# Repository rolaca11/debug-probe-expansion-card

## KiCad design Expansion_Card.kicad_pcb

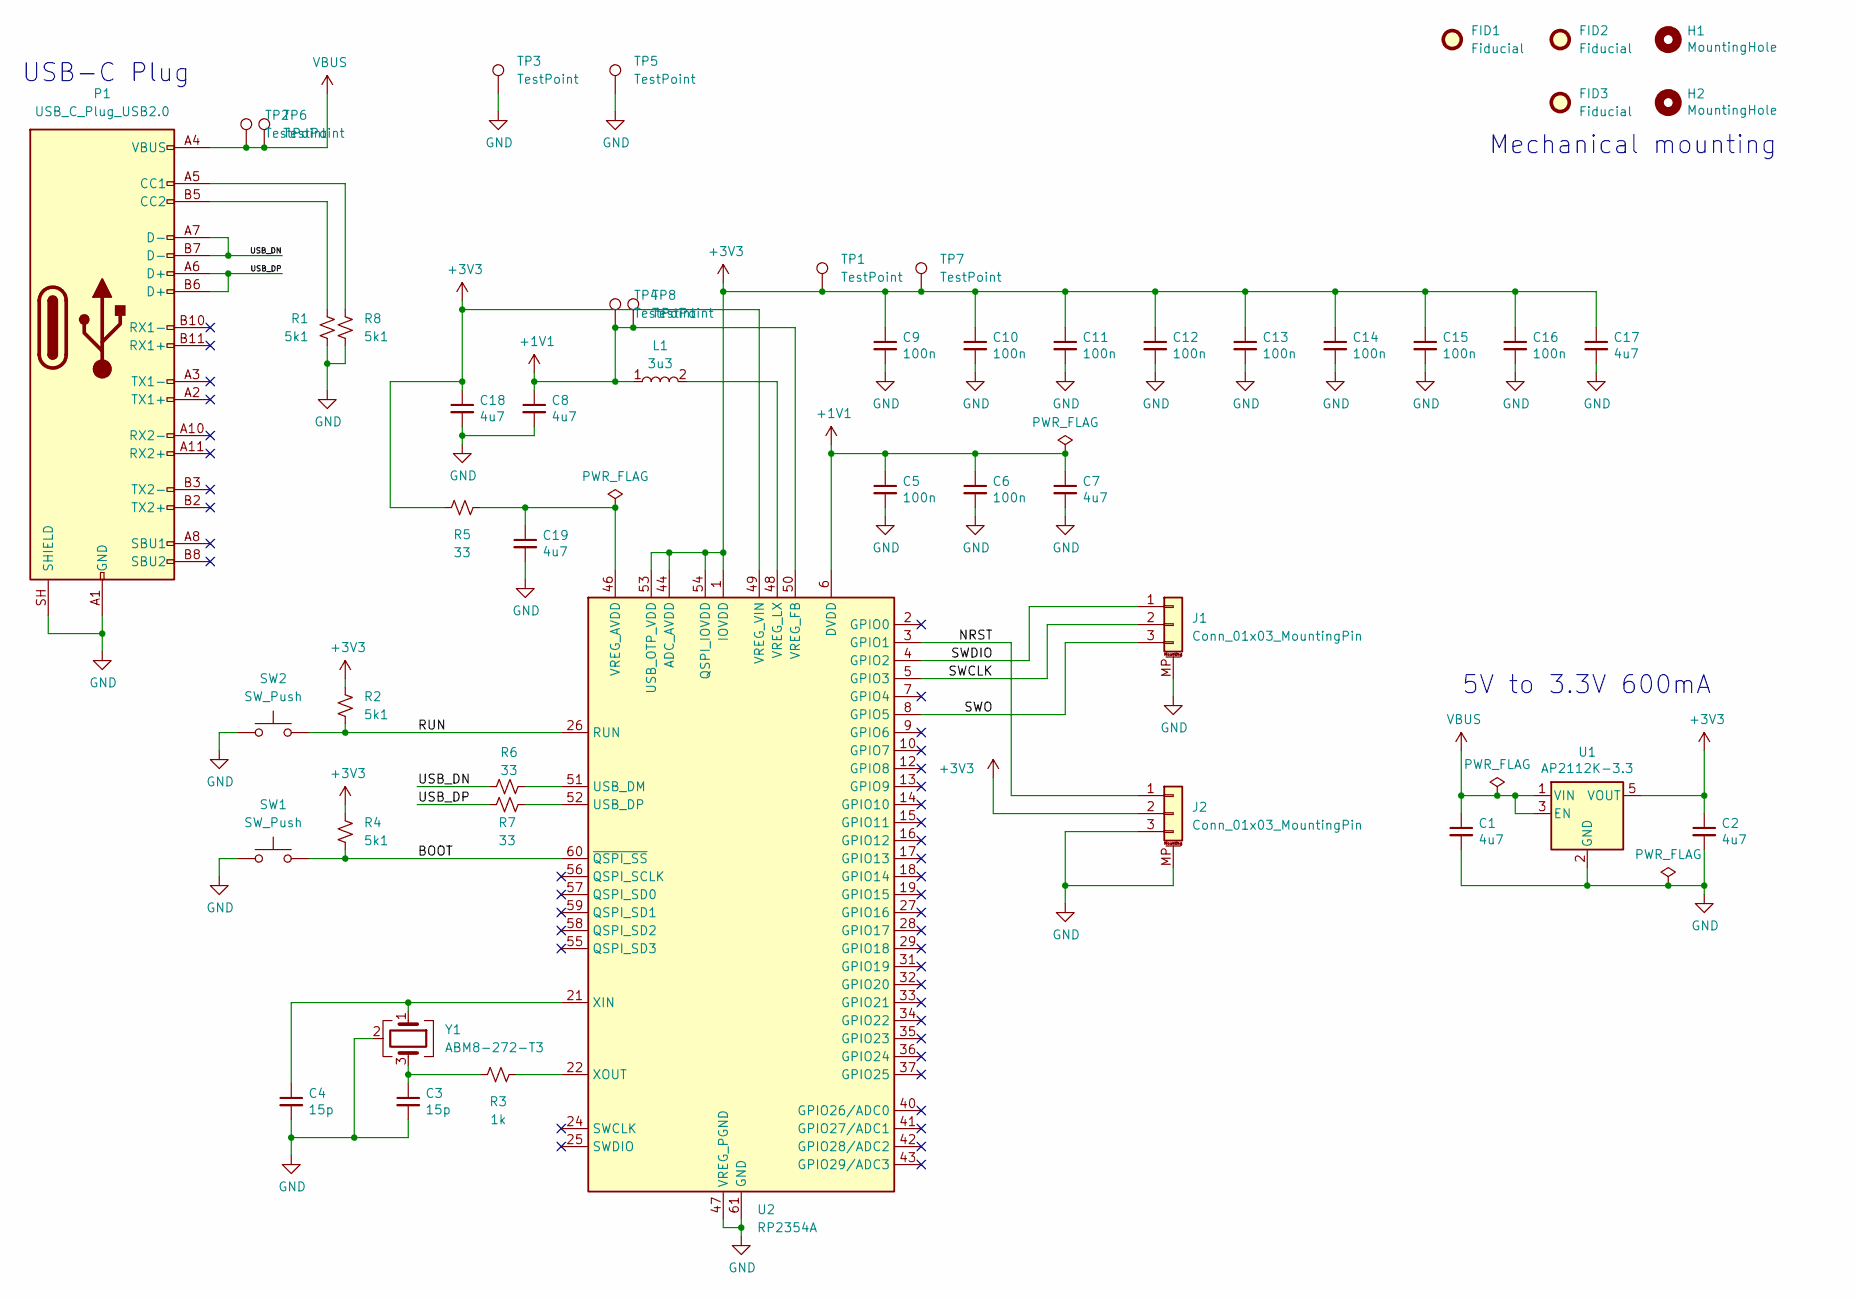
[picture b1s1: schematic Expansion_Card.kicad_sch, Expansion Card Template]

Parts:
C1, C2, C7, C8, C17, C18, C19: 4u7; C_0402_1005Metric; MPN CL05A475MP5NRNC; JLCPCB Part # C23733
C3, C4: 15p; C_0402_1005Metric; MPN 0402CG150J500NT; JLCPCB Part # C1548
C5, C6, C9, C10, C11, C12, C13, C14, C15, C16: 100n; C_0402_1005Metric; MPN CL05B104KO5NNNC; JLCPCB Part # C1525
FID1, FID2, FID3: Fiducial; Fiducial_1mm_Mask2mm
H1, H2: MountingHole; MountingHole_2.2mm_M2
J1, J2: Conn_01x03_MountingPin; JST_SH_SM03B-SRSS-TB_1x03-1MP_P1.00mm_Horizontal; MPN SM03B-SRSS-TB(LF)(SN); JLCPCB Part # C160403
L1: 3u3; AOTAB201610S3R3101T; MPN AOTA-B201610S3R3-101-T; JLCPCB Part # C42411119
P1: USB_C_Plug_USB2.0; USB_C_Plug_Molex_105444; MPN 1054440001; JLCPCB Part # C134082
R1, R2, R4, R8: 5k1; R_0402_1005Metric; MPN 0402WGF5101TCE; JLCPCB Part # C25905
R3: 1k; R_0402_1005Metric; MPN 0402WGF1001TCE; JLCPCB Part # C11702
R5, R6, R7: 33; R_0402_1005Metric; MPN 0402WGF330JTCE; JLCPCB Part # C25105
SW1, SW2: SW_Push; SW_SPST_B3U-1000P-B; MPN B3U-1000P; JLCPCB Part # C231329
TP1, TP2, TP3, TP4, TP5, TP6, TP7, TP8: TestPoint; TestPoint_Pad_D1.5mm
U1: AP2112K-3.3; SOT-23-5; MPN AP2112K-3.3TRG1; JLCPCB Part # C23380830
U2: RP2354A; QFN-60-1EP_7x7mm_P0.4mm_EP3.4x3.4mm; MPN RP2354A; JLCPCB Part # C41378174
Y1: ABM8-272-T3; Crystal_SMD_3225-4Pin_3.2x2.5mm; MPN ABM8-272-T3; JLCPCB Part # C20625731

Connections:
+1V1: C5.1, C6.1, C7.1, C8.1, L1.1, TP4.1 (1_1), TP8.1 (1_1), U2.6 (DVDD), U2.23 (DVDD), U2.39 (DVDD), U2.50 (VREG_FB)
+3V3: C2.1, C9.1, C10.1, C11.1, C12.1, C13.1, C14.1, C15.1, C16.1, C17.1, C18.1, J2.2, R2.2, R4.2, R5.1, TP1.1 (1_1), TP7.1 (1_1), U1.5 (VOUT), U2.1 (IOVDD), U2.11 (IOVDD), U2.20 (IOVDD), U2.30 (IOVDD), U2.38 (IOVDD), U2.44 (ADC_AVDD), U2.45 (IOVDD), U2.49 (VREG_VIN), U2.53 (USB_OTP_VDD), U2.54 (QSPI_IOVDD)
/BOOT: R4.1, SW1.2, U2.60 (~QSPI_SS)
/NRST: J2.1, U2.3 (GPIO1)
/RUN: R2.1, SW2.1, U2.26 (RUN)
/SWCLK: J1.2, U2.5 (GPIO3)
/SWDIO: J1.1, U2.4 (GPIO2)
/SWO: J1.3, U2.8 (GPIO5)
/USB_DN: P1.A7 (D-), P1.B7 (D-), R6.2
/USB_DP: P1.A6 (D+), P1.B6 (D+), R7.2
GND: C1.2, C2.2, C3.2, C4.2, C5.2, C6.2, C7.2, C8.2, C9.2, C10.2, C11.2, C12.2, C13.2, C14.2, C15.2, C16.2, C17.2, C18.2, C19.2, J1.MP (MountPin), J2.3, J2.MP (MountPin), P1.A1 (GND), P1.A12 (GND), P1.B1 (GND), P1.B12 (GND), P1.SH (SHIELD), R1.1, R8.2, SW1.1, SW2.2, TP3.1 (1_1), TP5.1 (1_1), U1.2 (GND), U2.47 (VREG_PGND), U2.61 (GND), Y1.2 (G), Y1.4 (G)
unnamed: C3.1, R3.1, Y1.3
unnamed: P1.A5 (CC1), R8.1
unnamed: P1.B5 (CC2), R1.2
unnamed: R6.1, U2.51 (USB_DM)
unnamed: R7.1, U2.52 (USB_DP)
unnamed: C19.1, R5.2, U2.46 (VREG_AVDD)
unnamed: L1.2, U2.48 (VREG_LX)
unnamed: C4.1, U2.21 (XIN), Y1.1
unnamed: R3.2, U2.22 (XOUT)
VBUS: C1.1, P1.A4 (VBUS), P1.A9 (VBUS), P1.B4 (VBUS), P1.B9 (VBUS), TP2.1 (1_1), TP6.1 (1_1), U1.1 (VIN), U1.3 (EN)

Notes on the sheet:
Mechanical mounting
USB-C Plug
5V to 3.3V 600mA

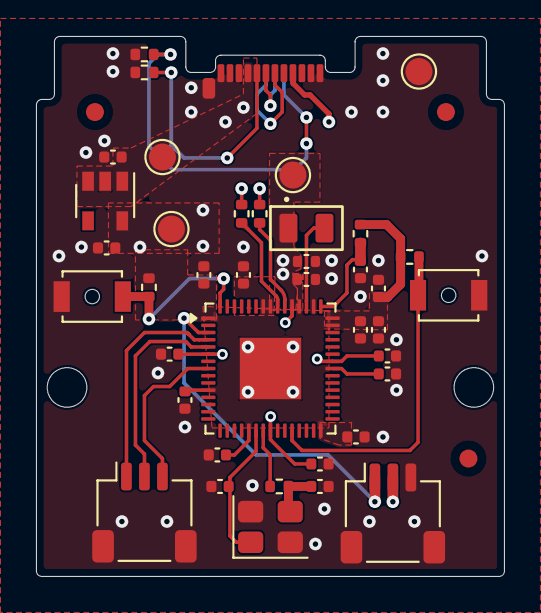
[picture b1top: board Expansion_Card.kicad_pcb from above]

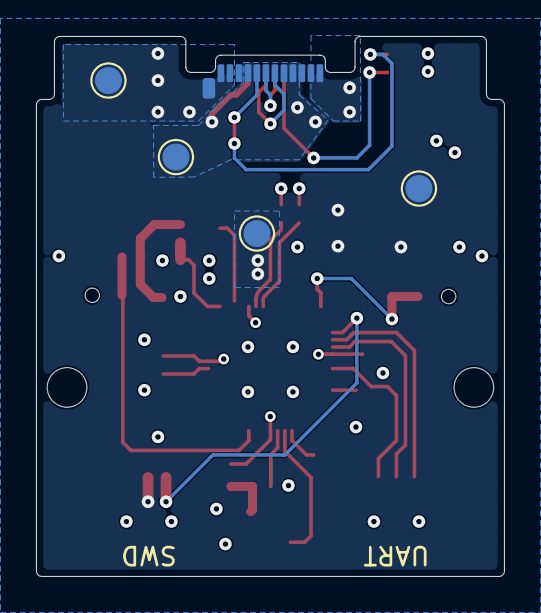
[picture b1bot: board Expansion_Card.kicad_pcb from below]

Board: 4 copper layers, 26.0 x 30.0 mm, 49 parts (4 on the bottom side), 21 nets.

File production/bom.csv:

Designator,Footprint,Quantity,Value,LCSC Part #
"C1, C17, C18, C19, C2, C7, C8",0402,7,4u7,C23733
"C10, C11, C12, C13, C14, C15, C16, C5, C6, C9",0402,10,100n,C1525
"C3, C4",0402,2,15p,C1548
"J1, J2",JST_SH_SM03B-SRSS-TB_1x03-1MP_P1.00mm_Horizontal,2,Conn_01x03_MountingPin,C160403
L1,AOTAB201610S3R3101T,1,3u3,C42411119
P1,USB_C_Plug_Molex_105444,1,USB_C_Plug_USB2.0,C134082
"R1, R2, R4, R8",0402,4,5k1,C25905
R3,0402,1,1k,C11702
"R5, R6, R7",0402,3,33,C25105
"SW1, SW2",SW_SPST_B3U-1000P-B,2,SW_Push,C231329
"TP1, TP2, TP3, TP4, TP5, TP6, TP7, TP8",TestPoint_Pad_D1.5mm,8,TestPoint,
U1,SOT-23-5,1,AP2112K-3.3,C23380830
U2,QFN-60-1EP_7x7mm_P0.4mm_EP3.4x3.4mm,1,RP2354A,C41378174
Y1,Crystal_SMD_3225-4Pin_3.2x2.5mm,1,ABM8-272-T3,C20625731

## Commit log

2026-04-24 add fiducials/testpoints
2026-04-24 export pdf
2026-04-24 chore

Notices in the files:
Expansion_Card.kicad_pcb:
This work is licensed under a Creative Commons Attribution 4.0 International License
